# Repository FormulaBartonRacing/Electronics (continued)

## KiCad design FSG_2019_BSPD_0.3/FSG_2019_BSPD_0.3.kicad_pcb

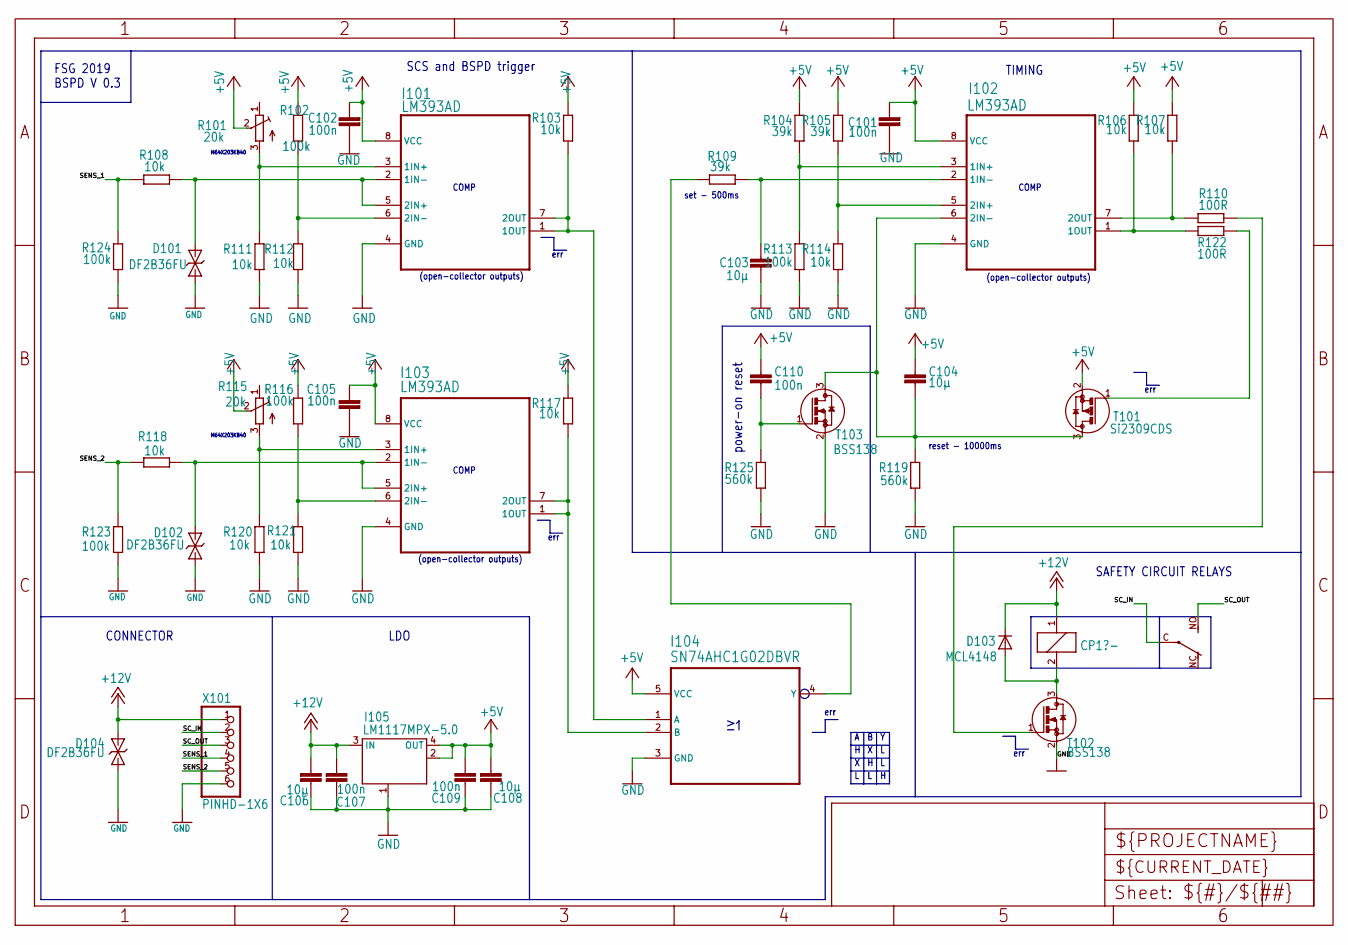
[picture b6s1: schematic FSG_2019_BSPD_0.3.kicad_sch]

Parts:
C101, C102, C105, C107, C109, C110: 100n; C0603
C103, C106, C108: 10µ; C1206
C104: 10µ; C1206K
D101, D102, D104: DF2B36FU; SOD323
D103: MCL4148; MICROMELF
I101, I102, I103: LM393AD; SOIC127P600X175-8N
I104: SN74AHC1G02DBVR; SOT95P280X145-5N
I105: LM1117MPX-5.0; LINEAR_SOT223
K101: CP1?-; CP1
R101, R115: 20k; M64X201KB40
R102, R113, R116, R123, R124: 100k; R0603
R103, R106, R107, R108, R111, R112, R114, R117, R118, R120, R121: 10k; R0603
R104, R105, R109: 39k; R0603
R110, R122: 100R; R0603
R119, R125: 560k; R0603
T101: Si2309CDS; SOT-23
T102, T103: BSS138; SOT-23
X101: PINHD-1X6; 1X06

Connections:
+5V: C101.2, C102.2, C104.1, C105.2, C108.1, C109.2, C110.1, I101.8 (VCC), I102.8 (VCC), I103.8 (VCC), I104.5 (VCC), I105.2 (OUT@1), I105.4 (OUT), R101.2 (M), R102.1, R103.1, R104.2, R105.2, R106.2, R107.2, R115.2 (M), R116.1, R117.1, T101.2 (S)
+12V: C106.1, C107.1, D103.C, D104.2 (C), I105.3 (IN), K101.1, X101.1
BRAKE_F: D101.2 (C), I101.2 (1IN-), I101.5 (2IN+), R108.2
DF: D102.2 (C), I103.2 (1IN-), I103.5 (2IN+), R118.2
GND: C101.1, C102.1, C103.2, C105.1, C106.2, C107.2, C108.2, C109.1, D101.1 (A), D102.1 (A), D104.1 (A), I101.4 (GND), I102.4 (GND), I103.4 (GND), I104.3 (GND), I105.1 (GND/ADJ), R111.2, R112.2, R113.1, R114.1, R119.1, R120.2, R121.2, R123.1, R124.1, R125.1, T102.2 (S), T103.2 (S), X101.6
unnamed: I102.5 (2IN+), R105.1, R114.2
unnamed: I103.1 (1OUT), I103.7 (2OUT), I104.2 (B), R117.2
unnamed: I101.1 (1OUT), I101.7 (2OUT), I104.1 (A), R103.2
unnamed: I102.1 (1OUT), R106.1, R122.2
unnamed: C110.2, R125.2, T103.1 (G)
unnamed: I101.3 (1IN+), R101.3 (A), R111.1
unnamed: C104.2, I102.6 (2IN-), R119.2, T101.3 (D), T103.3 (D)
unnamed: I103.3 (1IN+), R115.3 (A), R120.1
unnamed: R110.1, T102.1 (G)
unnamed: D103.A, K101.2, T102.3 (D)
unnamed: C103.1, I102.2 (1IN-), R109.1
unnamed: I102.3 (1IN+), R104.1, R113.2
unnamed: I101.6 (2IN-), R102.2, R112.1
unnamed: I102.7 (2OUT), R107.1, R110.2
unnamed: I103.6 (2IN-), R116.2, R121.1
unnamed: R122.1, T101.1 (G)
unnamed: I104.4 (Y), R109.2
SC_IN: K101.C, X101.2
SC_OUT: K101.NO (S), X101.3
SENS_1: R108.1, R124.2, X101.4
SENS_2: R118.1, R123.2, X101.5

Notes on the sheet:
(open-collector outputs)
err
M64X203KB40
set - 500ms
COMP
power-on reset
SCS and BSPD trigger
CONNECTOR
LDO
SAFETY CIRCUIT RELAYS
FSG 2019 BSPD V 0.3
reset - 10000ms
TIMING

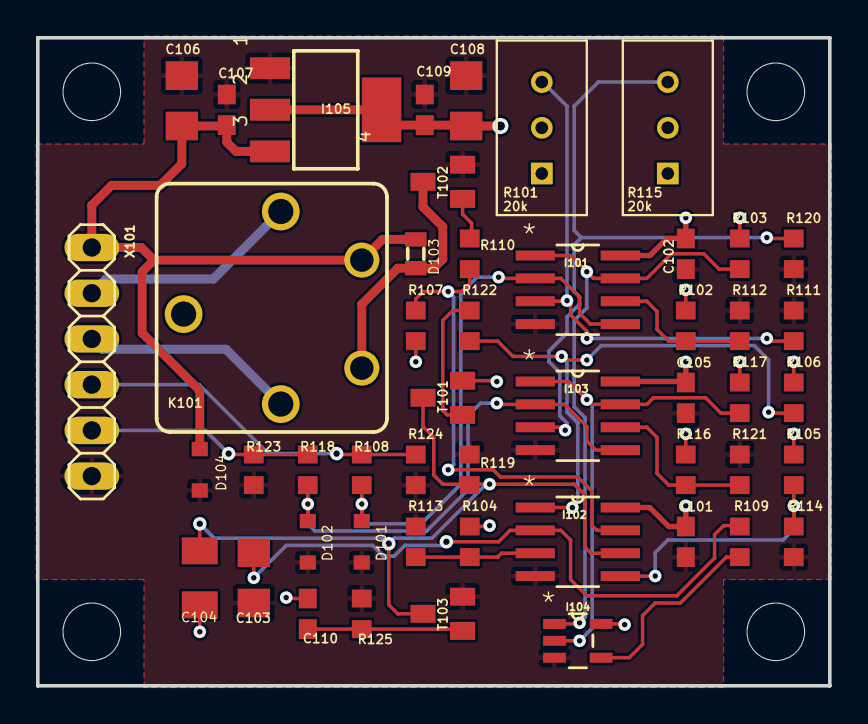
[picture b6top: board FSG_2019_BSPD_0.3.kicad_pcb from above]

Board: 2 copper layers, 44.0 x 36.0 mm, 53 parts (0 on the bottom side), 26 nets.

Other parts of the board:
@HOLE0, @HOLE1, @HOLE2, @HOLE3: (no value)

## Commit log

2024-09-25 Precharge v1.0
2024-09-25 FBR Logo
2024-10-06 v1.4
2024-10-06 Add FBR logo footprint
2024-10-06 Add .gitignore
2024-10-06 Remove unwanted backup and cache files
2024-10-06 Add FBR logo
2024-10-06 Precharge v1.4
2024-10-07 v1.4.1
2024-10-07 Updated resistor selection code
2024-10-07 v1.5
2024-10-11 v2.0
2024-10-11 modified gitignore
2024-10-13 v2.1
2024-10-20 v3.0 coming up
2025-01-02 ADD TSAL boards and MOD Precharge
2025-01-03 CREATE TSAL PCBs
2025-01-04 ADD 12x12 logo
2025-01-04 Add readme, sch pdf and pcb png
2025-01-04 v1.0.1
2025-01-06 Modify TSAL PCB and use relative paths for libraries
2025-01-14 Single signal connector
2025-01-14 Add FSG sample sch of BSPD
2025-01-14 minor changes
2025-02-07 update check
2025-02-27 Updated to KiCad v9
2025-02-27 Add BSPD board
2025-02-27 updating missed files
2025-02-28 Increase width of SDC track
2025-03-01 Corrected grid and place origins
2025-04-15 Precharge modifications
2025-04-15 Some modifications
2025-04-18 Add latest circuit PDFs
2025-04-18 Renamed and clleaned up Simulations
2025-05-04 Add PDIST
2025-06-06 Start Full System Circuit Diagram sch
2025-07-16 Corrected voltage threshold to 50.4V
2025-08-03 Modify Precharge PCB
2025-09-04 added hierarchichal labels for hierarchical sheet compatibility
2025-10-01 Pushing FluuSystemCircuit
2025-10-02 Add FullSystemCircuit
2026-01-15 Save corrupted files and new modifications
2026-01-15 Add plot of modified sch
2026-04-07 Resolve merge conflict
